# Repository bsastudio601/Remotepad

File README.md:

## Remotepad 
A macropad with 9 keys with a rotary encoder for voulume up and down. It was 12 SK6812 MINI-E LEDs around the keys for RGB lightning. The keys are wired in a matix configuration. It uses QMK firmware and VIA.

## CAD
The Remotepad!.

## Schematic
It uses a XIAO RP2040, 9 diodes, 9 mx cherry switches, 1 rotary encoder and 12 SK6812 MINI-E LEDs.

## PCB
I used 0.4mm traces is most parts and 0.6mm for the power connections.

## Case
The case is connected by four M3x16mm screws and four M3x5mx4mm heatset inserts. The case is printed in two parts, top and bottom

## Firmware
It uses QMK FIremwire I have plans to cutomize the layer to use them with my other projects like rover. for now it should have one singe layer.

## BOM

| Component | Quantity |
|-----------|----------|
| XIAO RP2040 | 1x |
| MX-Style Switch | 9x |
| 1N4148 Diode | 9x |
| Blank DSA keycaps | 9x | 
| 20cm Female-Female Jumper Wires | 8x | 
| 2.54mm 8 Pin Male Header | 1x | 
| 3.3V piezo Buzzer | 1x |
| M3x8mm Screws | 4x |
| M3x16mm Screws | 4x |
| M3x5mx4mm heatset inserts  |8x | 
| Custom PCB | 1x |
| 3D printed case | 1x |

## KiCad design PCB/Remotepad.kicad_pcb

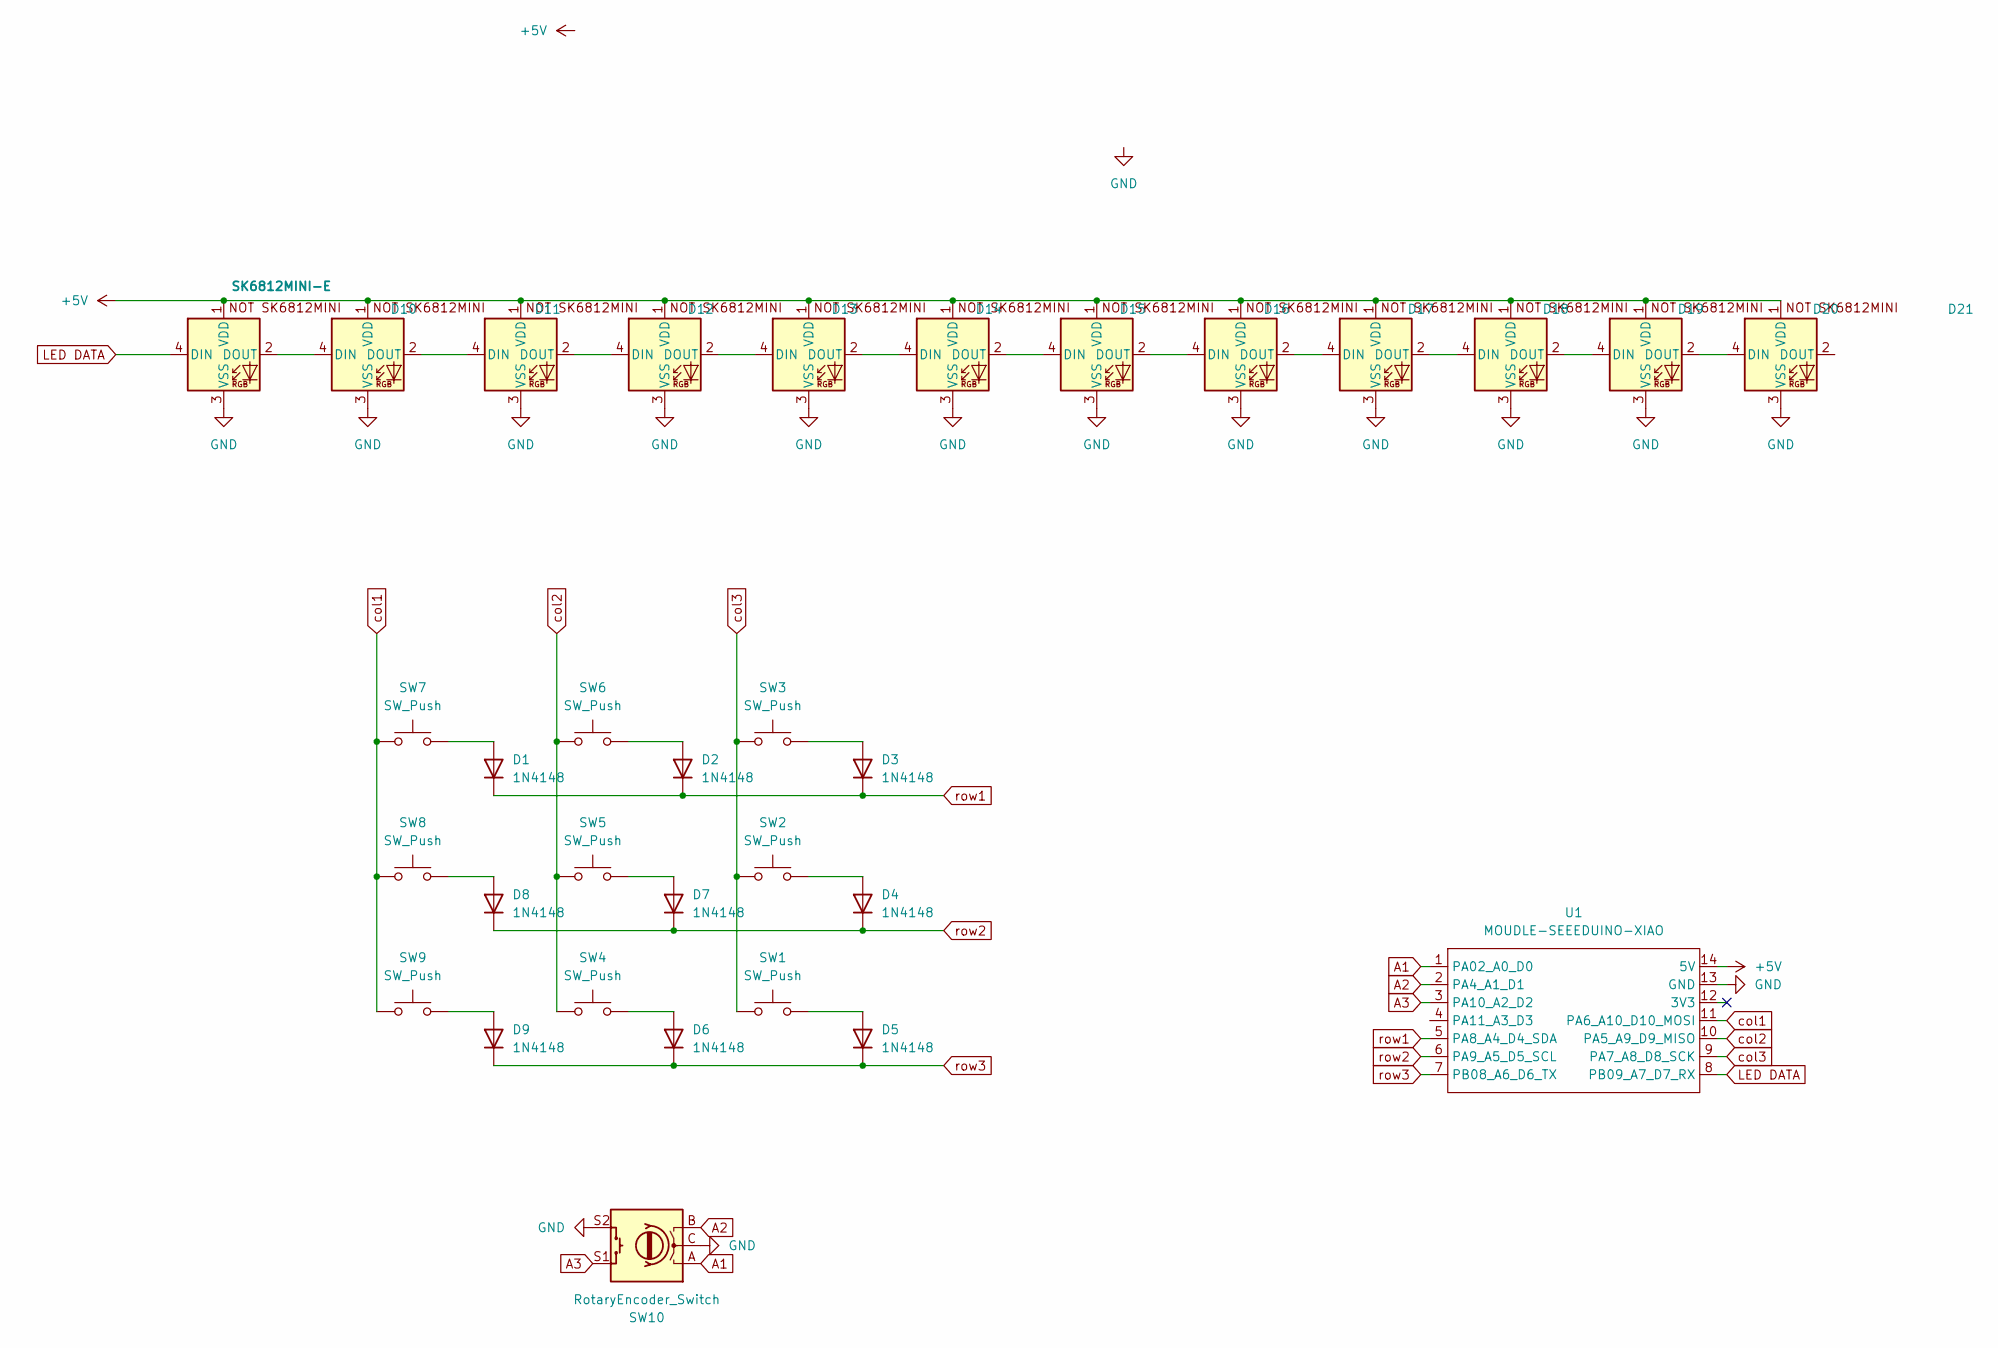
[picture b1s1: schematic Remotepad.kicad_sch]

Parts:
D1, D2, D3, D4, D5, D6, D7, D8, D9: 1N4148; D_DO-35_SOD27_P7.62mm_Horizontal
D10, D11, D12, D13, D14, D15, D16, D17, D18, D19, D20, D21: SK6812MINI-E; SK6812MINI-E_fixed
SW1, SW2, SW3, SW4, SW5, SW6, SW7, SW8, SW9: SW_Push; SW_Cherry_MX_1.00u_PCB
SW10: RotaryEncoder_Switch; RotaryEncoder_Alps_EC11E-Switch_Vertical_H20mm
U1: MOUDLE-SEEEDUINO-XIAO; XIAO-Generic-Hybrid-14P-2.54-21X17.8MM

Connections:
+5V: D10.1 (VDD), D11.1 (VDD), D12.1 (VDD), D13.1 (VDD), D14.1 (VDD), D15.1 (VDD), D16.1 (VDD), D17.1 (VDD), D18.1 (VDD), D19.1 (VDD), D20.1 (VDD), D21.1 (VDD), U1.14 (5V)
A1: SW10.A, U1.1 (PA02_A0_D0)
A2: SW10.B, U1.2 (PA4_A1_D1)
A3: SW10.S1, U1.3 (PA10_A2_D2)
GND: D10.3 (VSS), D11.3 (VSS), D12.3 (VSS), D13.3 (VSS), D14.3 (VSS), D15.3 (VSS), D16.3 (VSS), D17.3 (VSS), D18.3 (VSS), D19.3 (VSS), D20.3 (VSS), D21.3 (VSS), SW10.C, SW10.S2, U1.13 (GND)
LED DATA: D10.4 (DIN), U1.8 (PB09_A7_D7_RX)
unnamed: D1.2 (A), SW7.2
unnamed: D2.2 (A), SW6.2
unnamed: D3.2 (A), SW3.2
unnamed: D4.2 (A), SW2.2
unnamed: D5.2 (A), SW1.2
unnamed: D6.2 (A), SW4.2
unnamed: D7.2 (A), SW5.2
unnamed: D8.2 (A), SW8.2
unnamed: D9.2 (A), SW9.2
unnamed: D10.2 (DOUT), D11.4 (DIN)
unnamed: D11.2 (DOUT), D12.4 (DIN)
unnamed: D12.2 (DOUT), D13.4 (DIN)
unnamed: D13.2 (DOUT), D14.4 (DIN)
unnamed: D14.2 (DOUT), D15.4 (DIN)
unnamed: D15.2 (DOUT), D16.4 (DIN)
unnamed: D16.2 (DOUT), D17.4 (DIN)
unnamed: D17.2 (DOUT), D18.4 (DIN)
unnamed: D18.2 (DOUT), D19.4 (DIN)
unnamed: D19.2 (DOUT), D20.4 (DIN)
unnamed: D20.2 (DOUT), D21.4 (DIN)
col1: SW7.1, SW8.1, SW9.1, U1.11 (PA6_A10_D10_MOSI)
col2: SW4.1, SW5.1, SW6.1, U1.10 (PA5_A9_D9_MISO)
col3: SW1.1, SW2.1, SW3.1, U1.9 (PA7_A8_D8_SCK)
row1: D1.1 (K), D2.1 (K), D3.1 (K), U1.5 (PA8_A4_D4_SDA)
row2: D4.1 (K), D7.1 (K), D8.1 (K), U1.6 (PA9_A5_D5_SCL)
row3: D5.1 (K), D6.1 (K), D9.1 (K), U1.7 (PB08_A6_D6_TX)

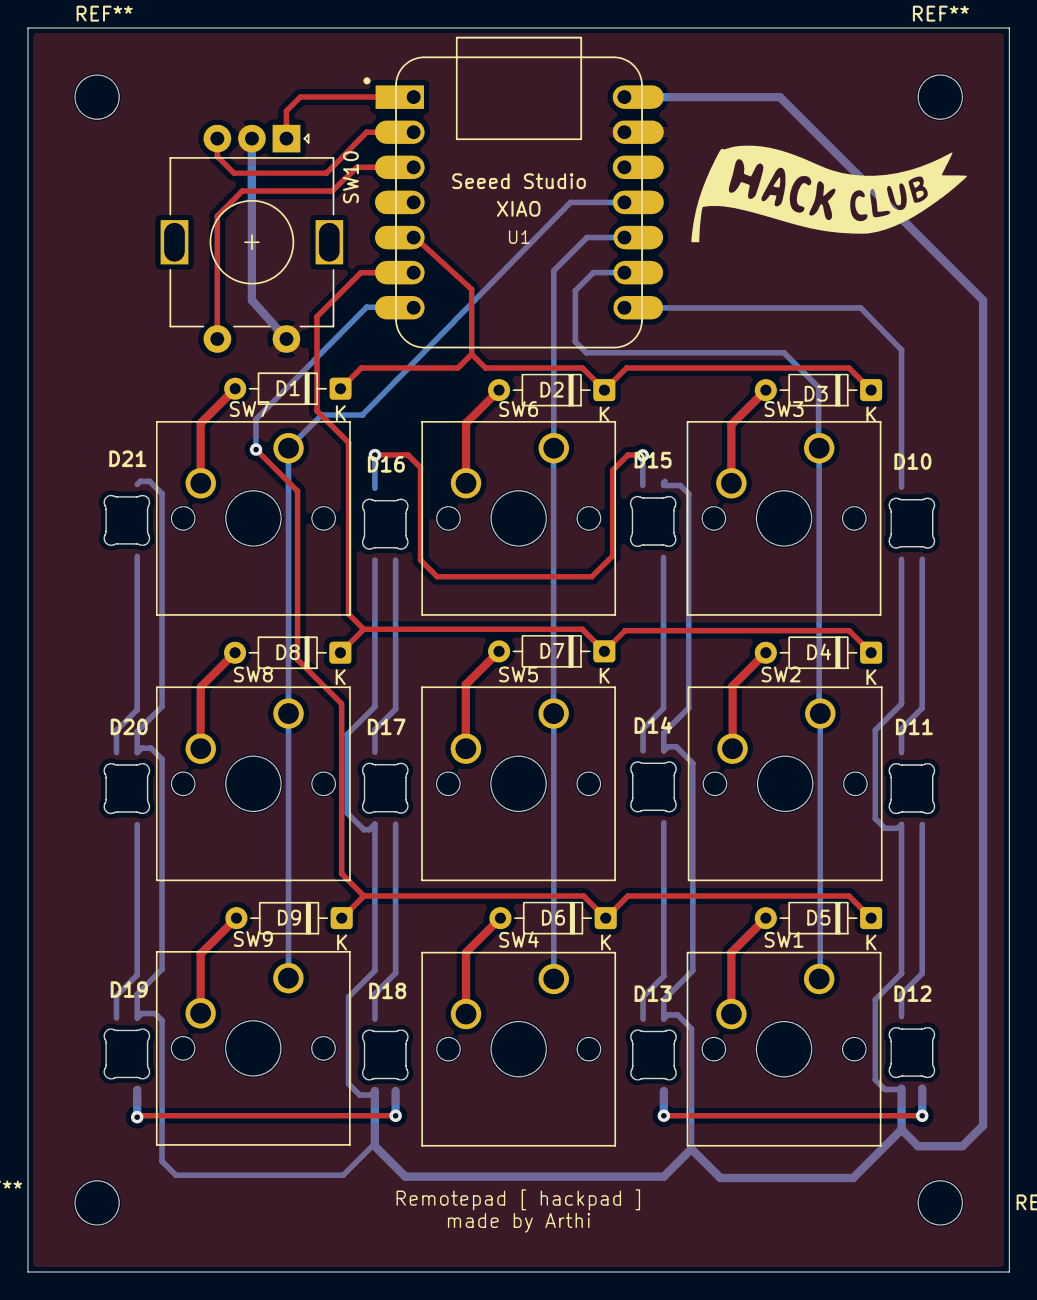
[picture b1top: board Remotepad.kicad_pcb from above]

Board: 4 copper layers, 71.0 x 89.9 mm, 32 parts (0 on the bottom side), 32 nets.

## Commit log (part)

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2026-06-17 Create the step file here
2026-06-17 Create the qmk file here
2026-06-17 Create the pcb stuff
2026-06-17 Create production files
2026-06-18 Create here
2026-06-18 Rename remotepad_default.uf2 to remotepad_firmware.uf2
2026-06-18 Rename Remotepad's case bottom.step to Bottom.step
2026-06-18 Rename Remotepad's case top.step to Top.step
2026-06-18 Rename remotepad_firmware.uf2 to Firmware.uf2
2026-06-19 Create Assets
2026-06-19 Rename Screenshot 2026-06-18 224013.png to CAD.png
2026-06-19 Rename Screenshot 2026-06-18 224133.png to CAD2.png
2026-06-19 Rename Screenshot 2026-06-18 232026.png to Schematic.png
2026-06-19 Rename Screenshot 2026-06-18 232150.png to PCB.png
2026-06-19 Update PCB trace specifications in README
    Clarified trace specifications for the PCB section.
2026-06-19 Rename CAD2png.png to CAD2.png
2026-06-19 Rename CADpng.png to CAD.png
2026-06-19 Rename gerber.zip to gerbers.zip
